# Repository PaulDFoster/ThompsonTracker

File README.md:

# ThompsonTracker
Hardware and Software for a simple BME280 and ESP8266 tracker

Issues:

1) RGB LED appears to always have D8 high (blue) *CRITICAL* Battery drain
2) CRC32bit, needs to be 8bit
3) HTTP post not implemented. Test HTTP Get is
4) EEPROM storage of readings not implemented
5) Clearing of EEPROM storage once readings confirmed uploaded not implemented
6) HTTP API Security not implemented

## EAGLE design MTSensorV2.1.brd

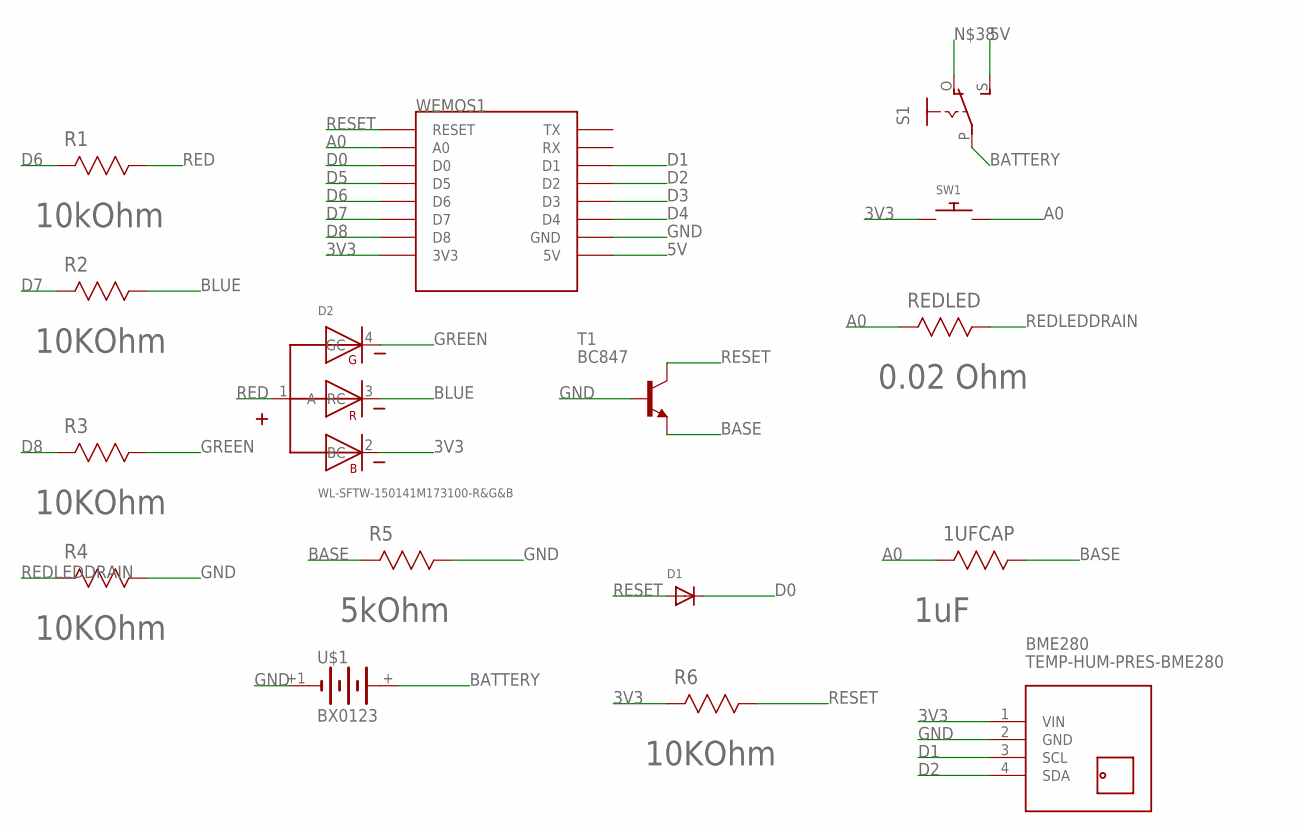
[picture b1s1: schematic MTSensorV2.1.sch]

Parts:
1UFCAP: 1uF; RESC1608X60N
BME280: TEMP-HUM-PRES-BME280
D1: DIODESOD-123; SOD-123
D2: WL-SFTW-150141M173100-R&G&B; 3528-COMMON-ANODE
R1: 10kOhm; RESC3216X71N
R2, R3, R4, R6: 10KOhm; RESC3216X71N
R5: 5kOhm; RESC3216X71N
REDLED: 0.02 Ohm; RESC3216X71N
S1: EG1218S; EG1218
SW1: SWITCH_PUSHBUTTONEVQ-PE; TACT_PANA-EVQ
T1: BC847; SOT23
U$1: BX0123; CR123A_HOLDER
WEMOS1: WEMOS-D1-MINI

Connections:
3V3: BME280.1 (VIN), D2.2 (BC), R6.2 (R2), SW1.P$1, WEMOS1.3V3
5V: S1.S, WEMOS1.5V
A0: 1UFCAP.2 (R2), REDLED.2 (R2), SW1.P$2, WEMOS1.A0
BASE: 1UFCAP.1 (R1), R5.2 (R2), T1.2 (E)
BATTERY: S1.P, U$1.+
BLUE: D2.3 (RC), R2.1 (R1)
D0: D1.C, WEMOS1.D0
D1: BME280.3 (SCL), WEMOS1.D1
D2: BME280.4 (SDA), WEMOS1.D2
D3: WEMOS1.D3
D4: WEMOS1.D4
D5: WEMOS1.D5
D6: R1.2 (R2), WEMOS1.D6
D7: R2.2 (R2), WEMOS1.D7
D8: R3.2 (R2), WEMOS1.D8
GND: BME280.2 (GND), R4.1 (R1), R5.1 (R1), T1.1 (B), U$1.+1 (-), WEMOS1.GND
GREEN: D2.4 (GC), R3.1 (R1)
RED: D2.1 (A), R1.1 (R1)
REDLEDDRAIN: R4.2 (R2), REDLED.1 (R1)
RESET: D1.A, R6.1 (R1), T1.3 (C), WEMOS1.RESET

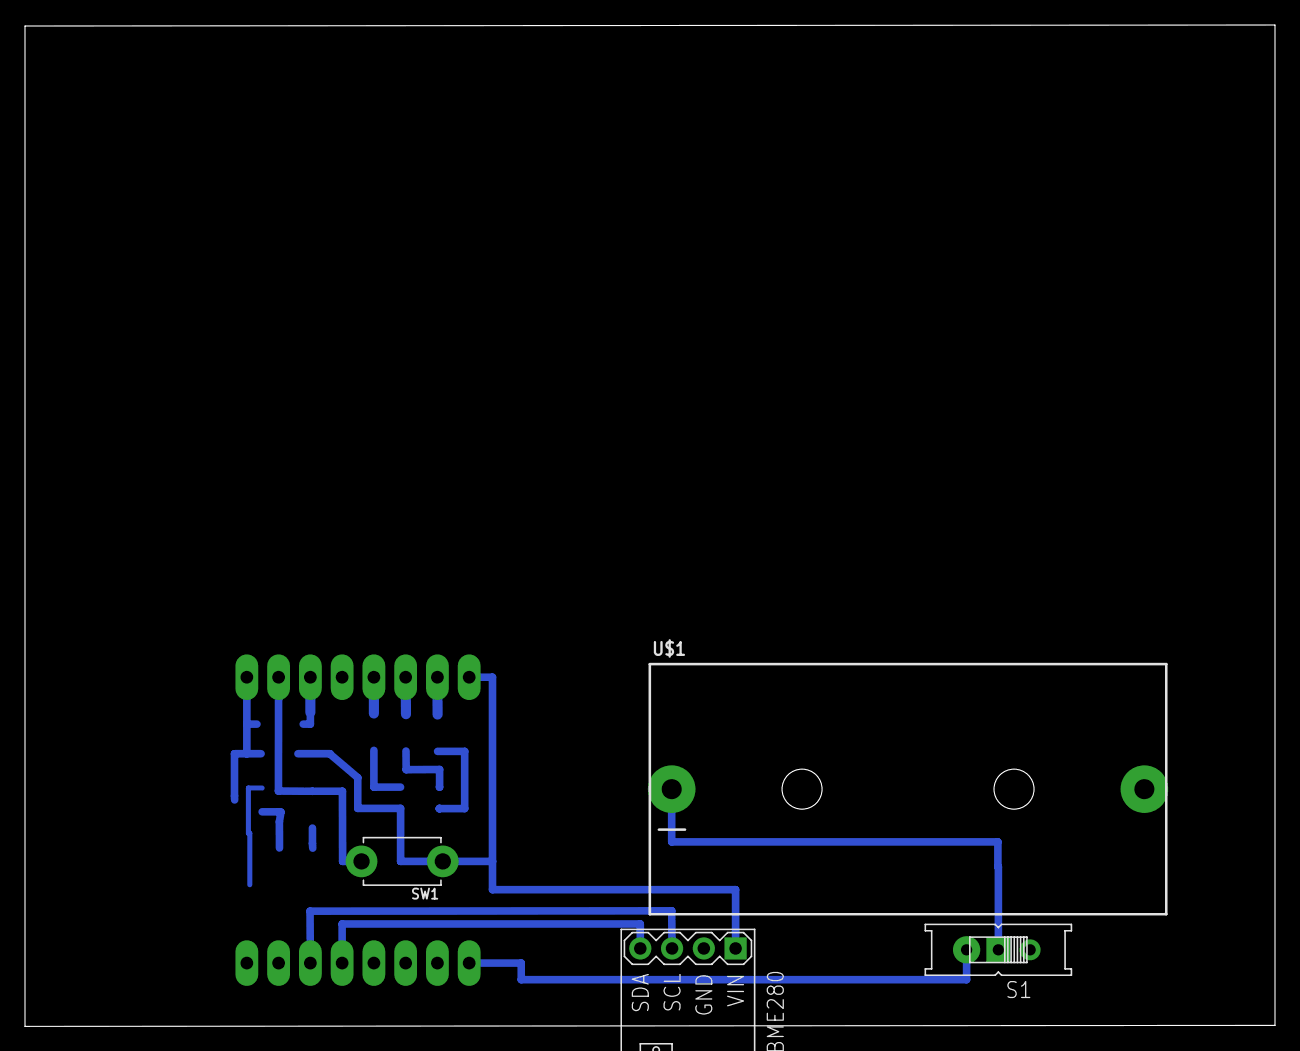
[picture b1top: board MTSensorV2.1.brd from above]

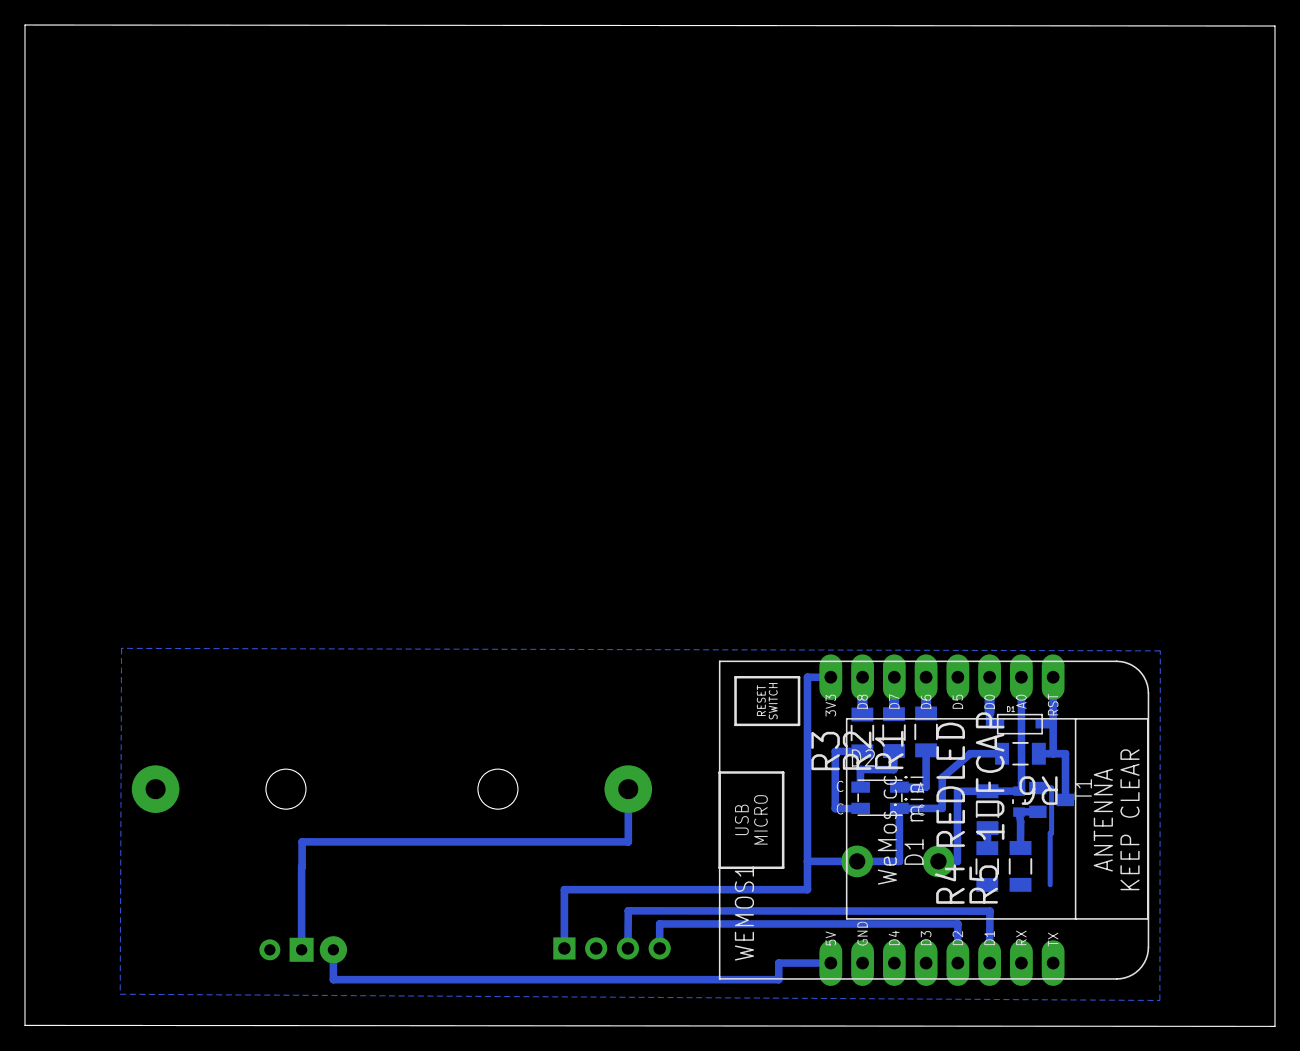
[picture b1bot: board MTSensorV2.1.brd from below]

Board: 2 copper layers, 100.0 x 80.1 mm, 16 parts (12 on the bottom side), 17 nets.

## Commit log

2018-04-17 Initial
    Issues still outstanding but functional

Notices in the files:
parts and their libraries:
diy-modules: Released under the Creative Commons Attribution 4.0 International License: http://creativecommons.org/licenses/by/4.0
Wurth_Elektronik_Optoelectronics_rev15b: Copyright: Würth Elektronik
